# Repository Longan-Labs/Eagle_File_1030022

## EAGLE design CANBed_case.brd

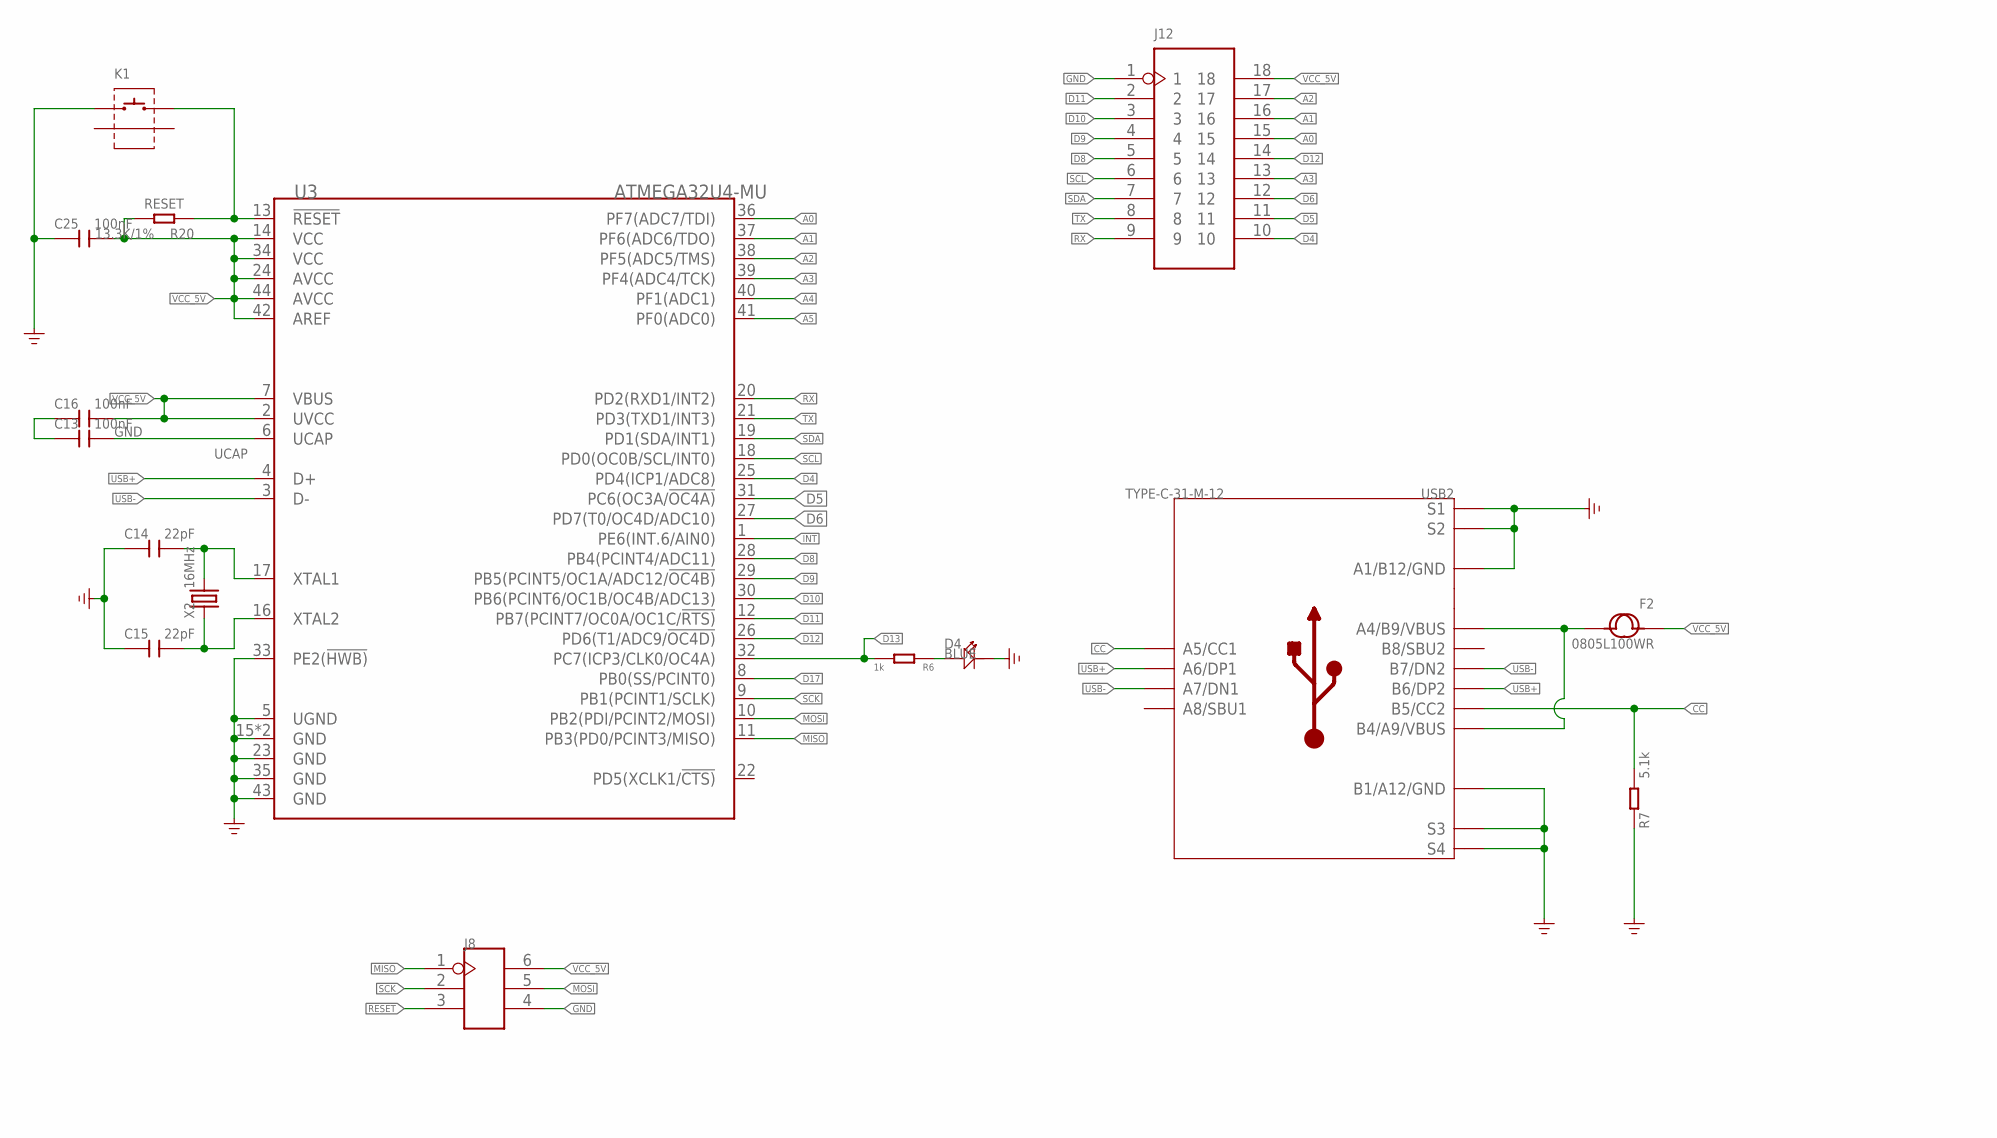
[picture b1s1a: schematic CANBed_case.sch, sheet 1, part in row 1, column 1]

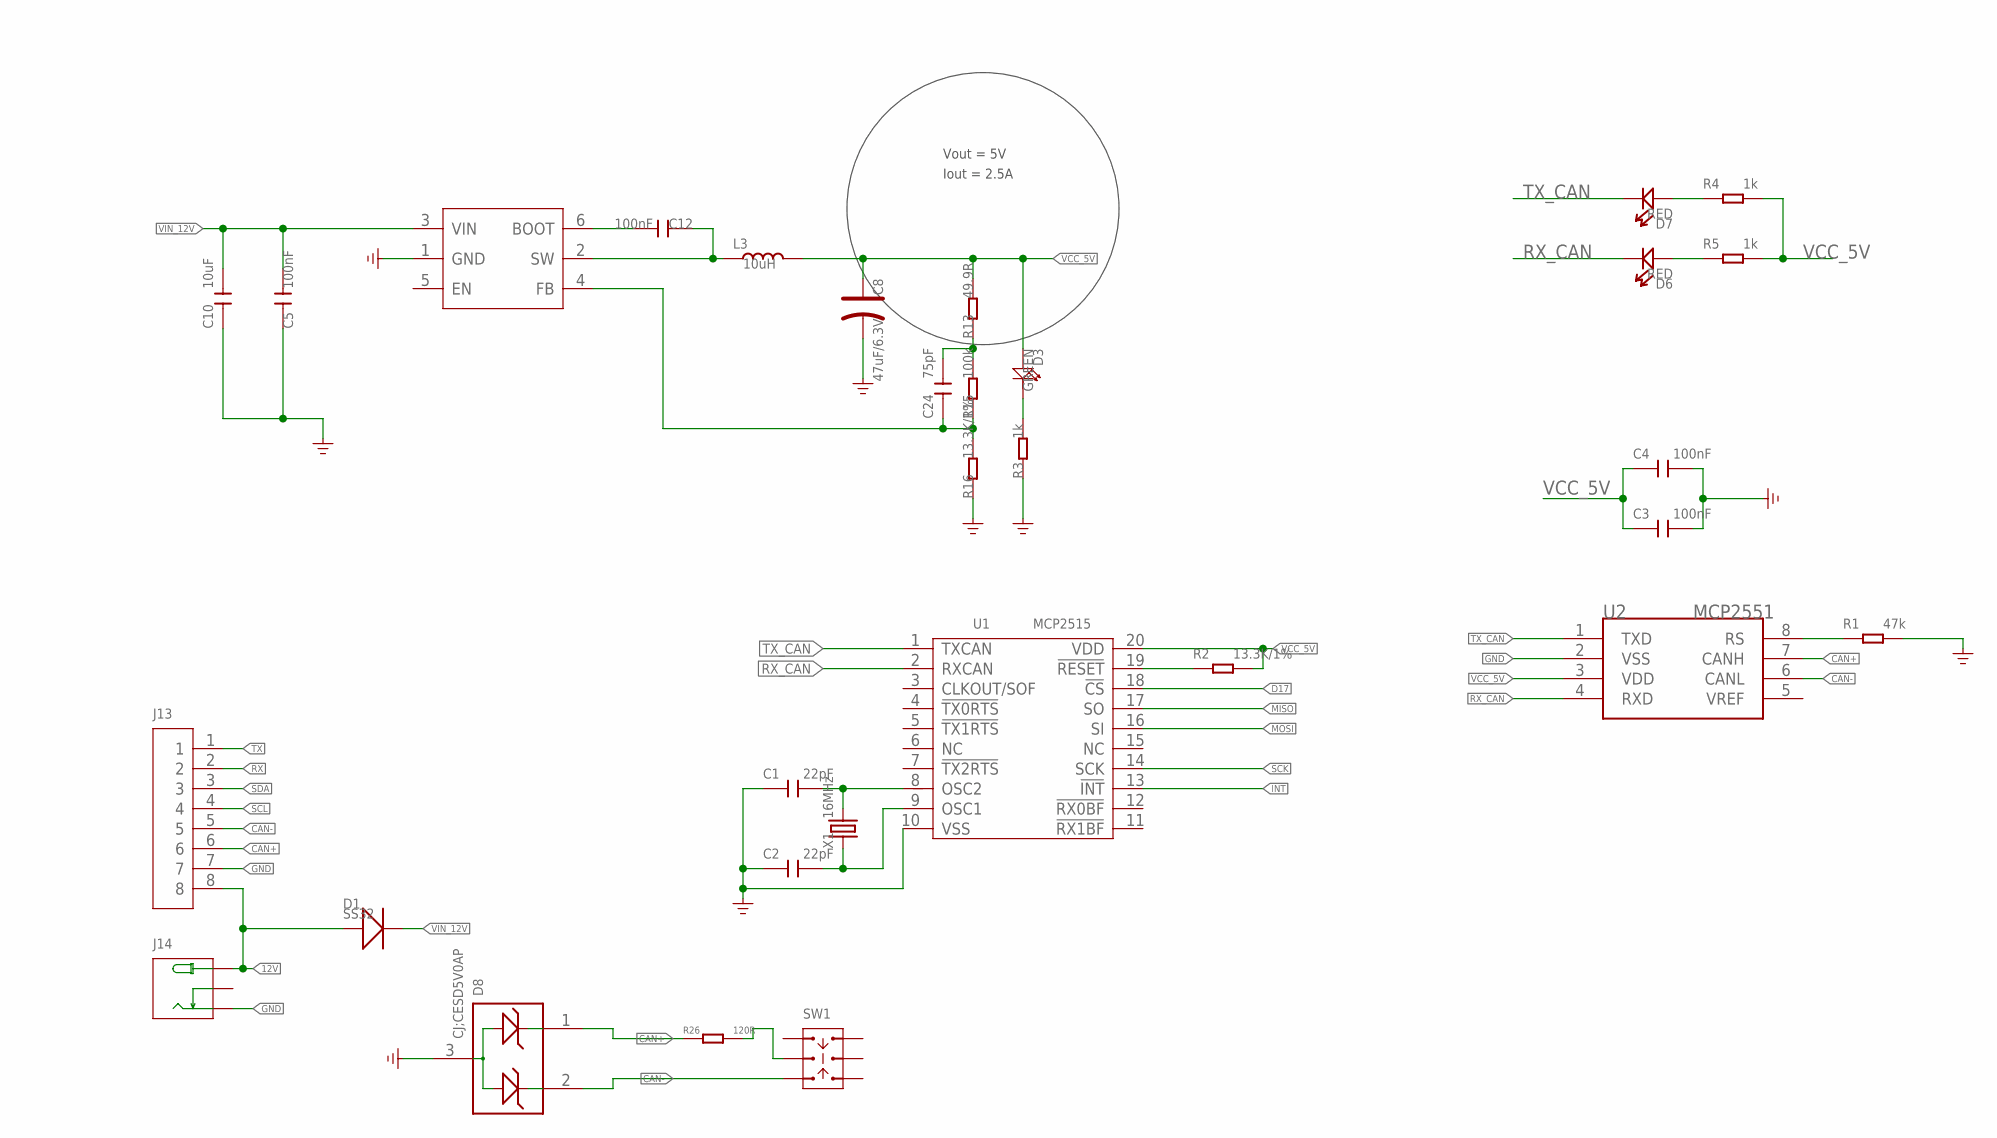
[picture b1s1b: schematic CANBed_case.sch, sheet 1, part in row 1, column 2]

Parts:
C1, C2, C14, C15: 22pF; C0603
C3, C4, C5, C12, C13, C16, C25: 100nF; C0603
C8: 47uF/6.3V; AVX-B
C10: 10uF; C1206
C24: 75pF; C0603
D1: SS32; DO-214AC
D3: GREEN; LED0805-SIDE
D4: BLUE; LED0805-SIDE
D6, D7: RED; LED-0603
D8: CJ;CESD5V0AP; SOT-23
F2: 0805L100WR; F0805
J8: HEADER-2X3P-2.54; H2X3-2.54
J12: HEADER-2X9P-2.54; H2X9-2.54
J13: TERMINAL-8P; TERMINAL8P-5.0-41.2X12.2X7.8MM
J14: POWER-JACK-DC-320120003; DCJ3P-14.2X11.0X9.0MM
K1: BUTTON-2+2P-K2-1102AQ; SW4-4.5-7X6.8X6MM
L3: 10uH; INT2-SMD-6.6X7.1X3MM
R1: 47k; R0603
R2, R16, R20: 13.3K/1%; R0603
R3, R4, R5, R6: 1k; R0603
R7: 5.1k; R0603
R13: 49.9R; R0603
R15: 100k; R0603
R26: 120R; R0603
SW1: SWITCH-2CH-6P-311010004; SW6-2.54-9.0X3.5X3.2+2.0MM
U1: MCP2515; TSSOP20-0.65-6.5X4.4MM
U2: MCP2551; SOIC8-6.0
U3: ATMEGA32U4-MU; QFN44G-0.5-7X7MM
U6: PMIC-TPS54302; SOT-23-6
USB2: TYPE-C-31-M-12; USB2.0-TYPE-C
X1, X2: 16MHz; X4-SMD-3.2X2.5X0.7MM

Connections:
12V: D1.1 (+), J13.8, J14.+
A0: J12.15, U3.36 (PF7(ADC7/TDI))
A1: J12.16, U3.37 (PF6(ADC6/TDO))
A2: J12.17, U3.38 (PF5(ADC5/TMS))
A3: J12.13, U3.39 (PF4(ADC4/TCK))
A4: U3.40 (PF1(ADC1))
A5: U3.41 (PF0(ADC0))
CAN+: D8.1, J13.6, R26.1, U2.7 (CANH)
CAN-: D8.2, J13.5, SW1.CH1B, U2.6 (CANL)
CC: R7.2, USB2.A5 (A5/CC1), USB2.B5 (B5/CC2)
D4: J12.10, U3.25 (PD4(ICP1/ADC8))
D5: J12.11, U3.31 (PC6(OC3A/!OC4A))
D6: J12.12, U3.27 (PD7(T0/OC4D/ADC10))
D8: J12.5, U3.28 (PB4(PCINT4/ADC11))
D9: J12.4, U3.29 (PB5(PCINT5/OC1A/ADC12/!OC4B))
D10: J12.3, U3.30 (PB6(PCINT6/OC1B/OC4B/ADC13))
D11: J12.2, U3.12 (PB7(PCINT7/OC0A/OC1C/!RTS))
D12: J12.14, U3.26 (PD6(T1/ADC9/!OC4D))
D13: R6.2, U3.32 (PC7(ICP3/CLK0/OC4A))
D17: U1.18 (!CS), U3.8 (PB0(SS/PCINT0))
GND: C1.1, C2.1, C3.2, C4.2, C5.1, C8.-, C10.1, C13.1, C14.1, C15.1, C16.1, C25.1, D4.-, D8.3, J8.4, J12.1, J13.7, J14.-1 (-), K1.1, R1.2, R3.1, R7.1, R16.1, U1.10 (VSS), U2.2 (VSS), U3.5 (UGND), U3.15 (GND), U3.23 (GND), U3.33 (PE2(!HWB)), U3.35 (GND), U3.43 (GND), U3.TAB (GND), U6.1 (GND), USB2.A1_B12 (A1/B12/GND), USB2.B1_A12 (B1/A12/GND), USB2.S1, USB2.S2, USB2.S3, USB2.S4, USB2.S5 (S1), USB2.S6 (S2)
INT: U1.13 (!INT), U3.1 (PE6(INT.6/AIN0))
MISO: J8.1, U1.17 (SO), U3.11 (PB3(PD0/PCINT3/MISO))
MOSI: J8.5, U1.16 (SI), U3.10 (PB2(PDI/PCINT2/MOSI))
unnamed: D3.-, R3.2
unnamed: D7.+, R4.1
unnamed: F2.2, USB2.A4_B9 (A4/B9/VBUS), USB2.B4_A9 (B4/A9/VBUS)
unnamed: R26.2, SW1.COM1
unnamed: C14.2, U3.17 (XTAL1), X2.3 (2)
unnamed: D4.+, R6.1
unnamed: C12.1, L3.1, U6.2 (SW)
unnamed: C15.2, U3.16 (XTAL2), X2.1
unnamed: C12.2, U6.6 (BOOT)
unnamed: D6.+, R5.1
unnamed: C1.2, U1.8 (OSC2), X1.3 (2)
unnamed: C2.2, U1.9 (OSC1), X1.1
unnamed: R1.1, U2.8 (RS)
unnamed: C24.2, R13.1, R15.2
unnamed: C24.1, R15.1, R16.2, U6.4 (FB)
RESET: J8.3, K1.2, R20.1, U3.13 (!RESET)
RST_N: R2.1, U1.19 (!RESET)
RX: J12.9, J13.2, U3.20 (PD2(RXD1/INT2))
RX_CAN: D6.-, U1.2 (RXCAN), U2.4 (RXD)
SCK: J8.2, U1.14 (SCK), U3.9 (PB1(PCINT1/SCLK))
SCL: J12.6, J13.4, U3.18 (PD0(OC0B/SCL/INT0))
SDA: J12.7, J13.3, U3.19 (PD1(SDA/INT1))
TX: J12.8, J13.1, U3.21 (PD3(TXD1/INT3))
TX_CAN: D7.-, U1.1 (TXCAN), U2.1 (TXD)
UCAP: C13.2, U3.6 (UCAP)
USB+: U3.4 (D+), USB2.A6 (A6/DP1), USB2.B6 (B6/DP2)
USB-: U3.3 (D-), USB2.A7 (A7/DN1), USB2.B7 (B7/DN2)
VCC_5V: C3.1, C4.1, C8.+, C16.2, C25.2, D3.+, F2.1, J8.6, J12.18, L3.2, R2.2, R4.2, R5.2, R13.2, R20.2, U1.20 (VDD), U2.3 (VDD), U3.2 (UVCC), U3.7 (VBUS), U3.14 (VCC), U3.24 (AVCC), U3.34 (VCC), U3.42 (AREF), U3.44 (AVCC)
VIN_12V: C5.2, C10.2, D1.2 (-), U6.3 (VIN)

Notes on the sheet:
Vout = 5V
Iout = 2.5A

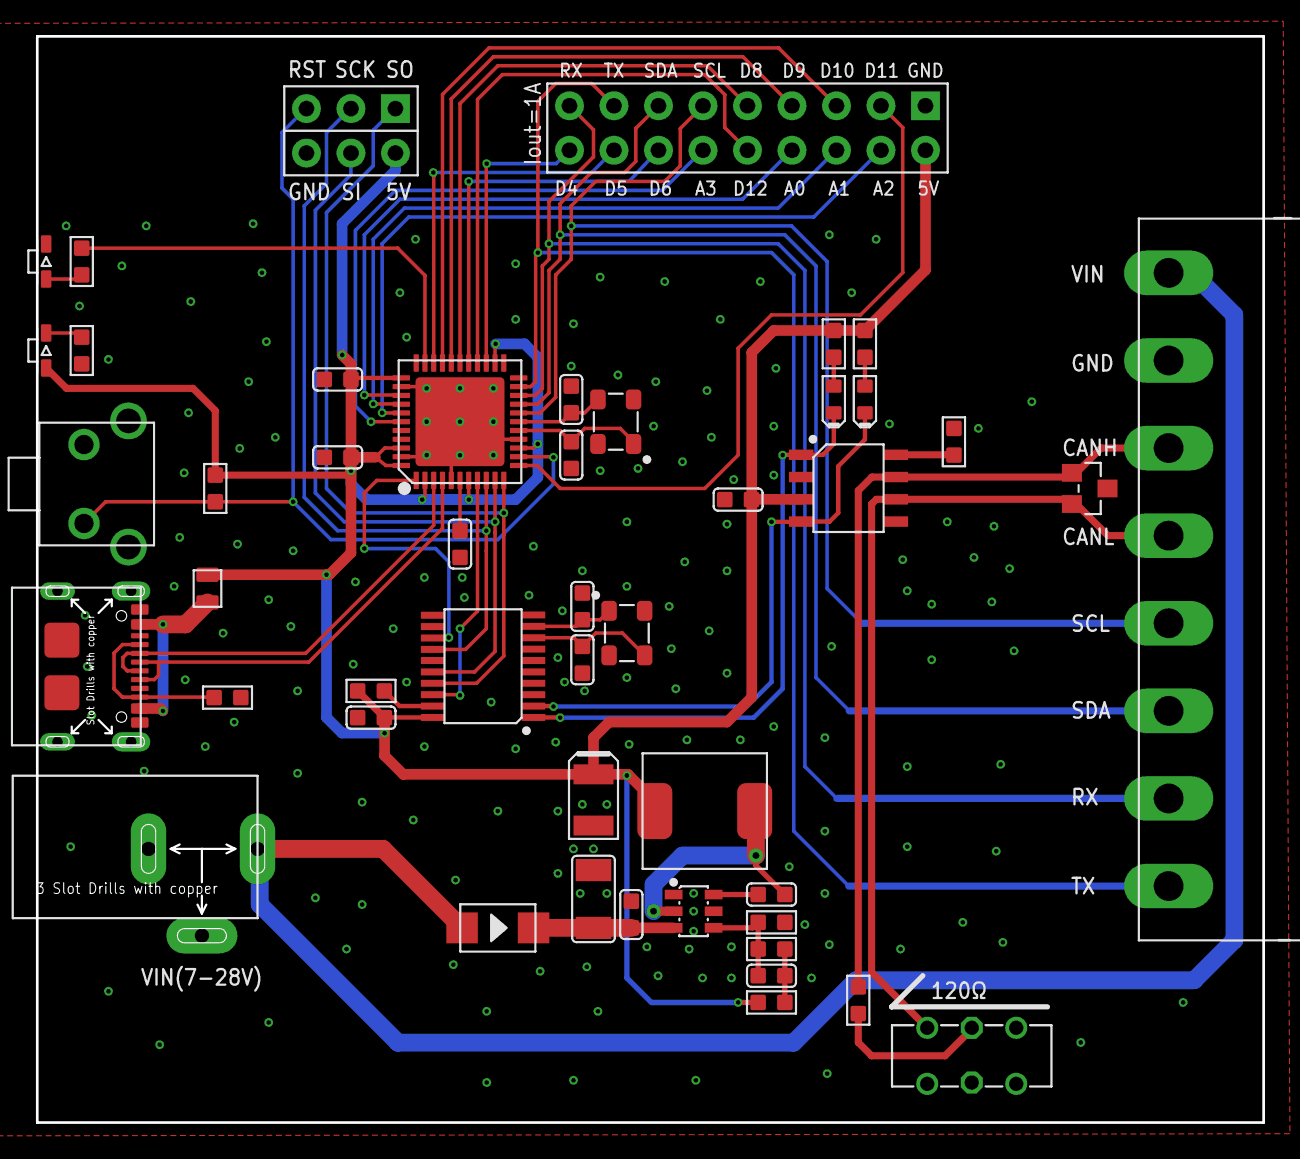
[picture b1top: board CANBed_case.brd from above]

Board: 2 copper layers, 70.0 x 62.0 mm, 48 parts (1 on the bottom side), 51 nets.

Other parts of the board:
U$5: LONGAN-SILK-SMALL

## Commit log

2023-01-08 add file
